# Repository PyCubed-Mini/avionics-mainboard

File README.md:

# avionics-motherboard
Main flight computer board for the PyCubed-Mini spacecraft

[Motherboard block diagram draw.io](https://drive.google.com/file/d/1i8R7Gf3Xthh23wCwzEqk22y6YbL8fg8w/view?usp=sharing)

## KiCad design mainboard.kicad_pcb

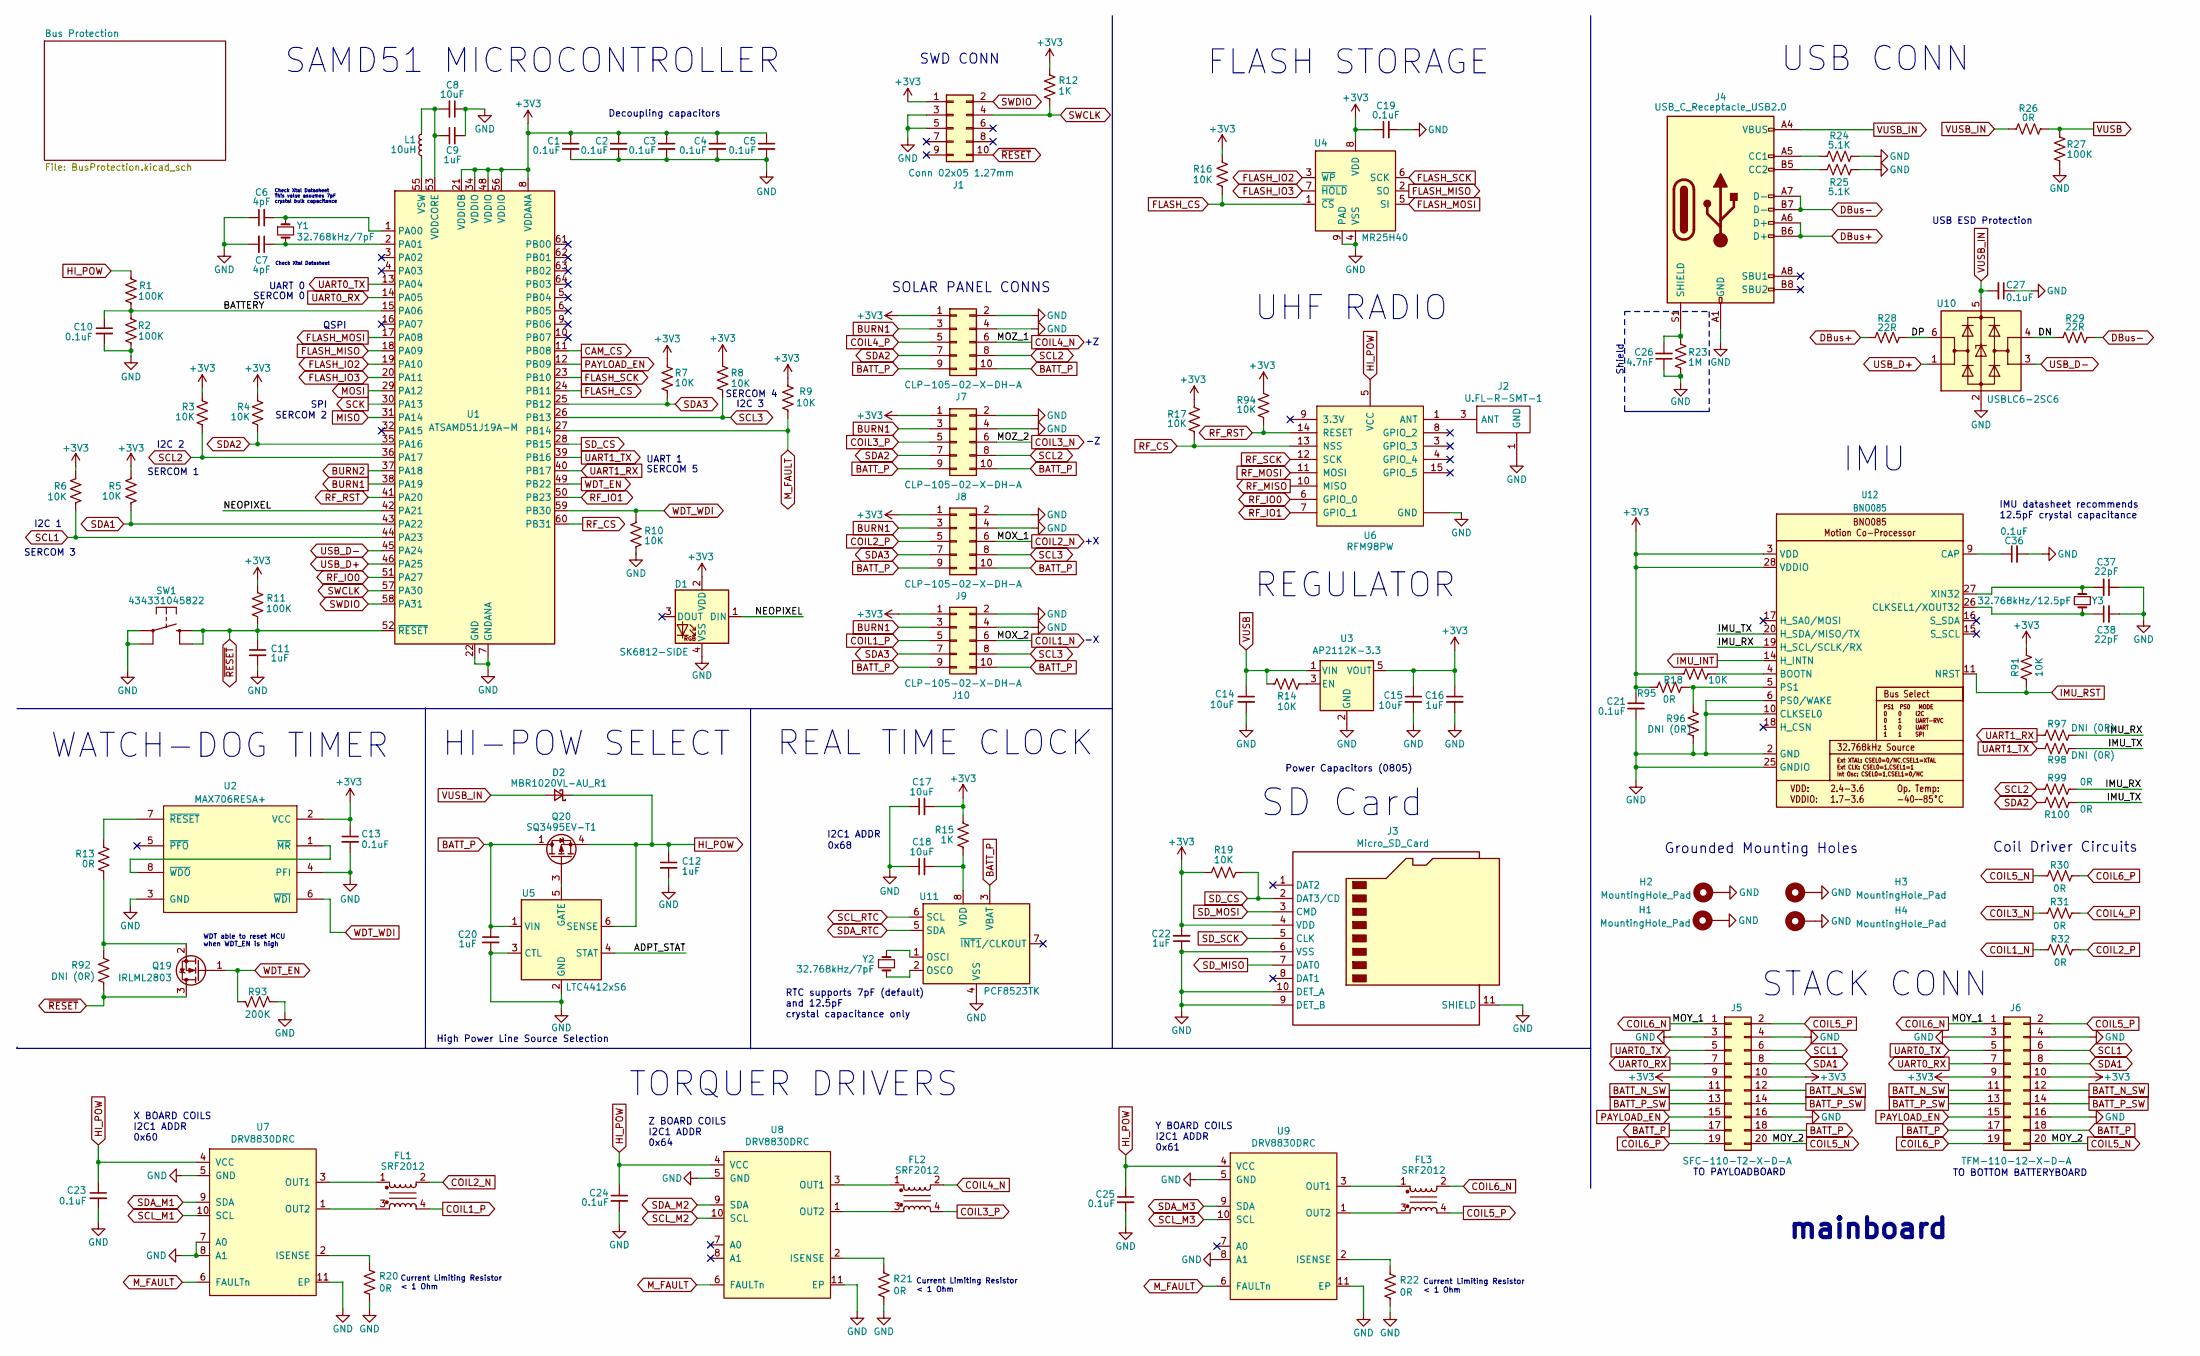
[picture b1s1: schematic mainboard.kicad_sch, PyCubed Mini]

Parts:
C1, C2, C3, C4, C5, C10, C13, C19, C21, C23, C24, C25, C27, C36: 0.1uF; C_0603_1608Metric
C6, C7: 4pF; C_0603_1608Metric
C8, C17, C18: 10uF; C_0603_1608Metric
C9, C11, C12, C20, C22: 1uF; C_0603_1608Metric
C14, C15: 10uF; C_0805_2012Metric
C16: 1uF; C_0805_2012Metric
C26: 4.7nF; C_0603_1608Metric
C37, C38: 22pF; C_0603_1608Metric
D1: SK6812-SIDE
D2: MBR1020VL-AU_R1; D_SOD-123F
FL1, FL2, FL3: SRF2012
H1, H2, H3, H4: MountingHole_Pad; MountingHole
J1: Conn 02x05 1.27mm; PinHeader_2x05_P1.27mm_Vertical_SMD
J2: U.FL-R-SMT-1; Manufacturer_Part_Number U.FL-R-SMT-1
J3: Micro_SD_Card; microSD_104031-0811
J4: USB_C_Receptacle_USB2.0; USB_C_Receptacle_HRO_TYPE-C-31-M-12
J5: SFC-110-T2-X-D-A; SAMTEC_SFC-110-T2-X-D-A
J6: TFM-110-12-X-D-A; SAMTEC_TFM-110-12-X-D-A
J7, J8, J9, J10: CLP-105-02-X-DH-A; SAMTEC_CLP-105-02-X-DH-A
L1: 10uH; L_0805_2012Metric
Q19: IRLML2803; SOT-23
Q20: SQ3495EV-T1; SOT-23-6
R1, R2, R11, R27: 100K; R_0603_1608Metric
R3, R4, R5, R6, R7, R8, R9, R10, R14, R16, R17, R18, R19, R91, R94: 10K; R_0603_1608Metric
R12, R15: 1K; R_0603_1608Metric
R13, R20, R21, R22, R26, R30, R31, R32, R95, R99, R100: 0R; R_0603_1608Metric
R23: 1M; R_0603_1608Metric
R24, R25: 5.1K; R_0603_1608Metric
R28, R29: 22R; R_0603_1608Metric
R92, R96, R97, R98: DNI (0R); R_0603_1608Metric
R93: 200K; R_0603_1608Metric
SW1: 434331045822; SMT_1045822_WRE
U1: ATSAMD51J19A-M; QFN-64-1EP_9x9mm_P0.5mm_EP4.7x4.7mm
U2: MAX706RESA+; SOIC-8_3.9x4.9mm_P1.27mm
U3: AP2112K-3.3; SOT-23-5
U4: MR25H40; MR25H40DF
U5: LTC4412xS6; TSOT-23-6
U6: RFM98PW
U7, U8, U9: DRV8830DRC; VSON-10
U10: USBLC6-2SC6; SOT-23-6
U11: PCF8523TK; HVSON-8-1EP_4x4mm_P0.8mm_EP2.2x3.1mm
U12: BNO085; LGA-28
Y1, Y2: 32.768kHz/7pF; Crystal_SMD_MicroCrystal_CC7V-T1A-2Pin_3.2x1.5mm
Y3: 32.768kHz/12.5pF; Crystal_SMD_MicroCrystal_CC7V-T1A-2Pin_3.2x1.5mm

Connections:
+3V3: C1.1, C2.1, C3.1, C4.1, C5.1, C13.1, C15.1, C16.1, C17.2, C19.1, C21.1, C22.2, D1.2 (VDD), J1.1, J3.4 (VDD), J5.9, J5.10, J6.9, J6.10, J7.1, J8.1, J9.1, J10.1, R3.2, R4.2, R5.2, R6.2, R7.2, R8.2, R9.1, R11.2, R12.2, R15.2, R16.1, R17.2, R18.2, R19.1, R91.2, R94.2, R95.2, U1.8 (VDDANA), U1.21 (VDDIOB), U1.34 (VDDIO), U1.48 (VDDIO), U1.56 (VDDIO), U2.2 (VCC), U3.5 (VOUT), U4.8 (VDD), U12.3 (VDD), U12.28 (VDDIO); also elsewhere on the board
/ADPT_STAT: U5.4 (STAT)
/BATTERY: C10.1, R1.1, R2.2, U1.15 (PA06)
/DN: R29.2, U10.4 (I/O2)
/DP: R28.1, U10.6 (I/O1)
/IMU_RX: R97.2, R99.2, U12.19 (H_SCL/SCLK/RX)
/IMU_TX: R98.2, R100.2, U12.20 (H_SDA/MISO/TX)
/NEOPIXEL: D1.1 (DIN), U1.42 (PA21)
BATT_N_SW: J5.11, J5.12, J6.11, J6.12
BATT_P: C20.1, J5.17, J5.18, J6.17, J6.18, J7.9, J7.10, J8.9, J8.10, J9.9, J9.10, J10.9, J10.10, Q20.1 (D), Q20.2 (D), Q20.5 (D), Q20.6 (D), U5.1 (VIN), U11.3 (VBAT)
BATT_P_SW: J5.13, J5.14, J6.13, J6.14
BURN1: J7.3, J8.3, J9.3, J10.3, U1.38 (PA19)
BURN2: U1.37 (PA18)
CAM_CS: U1.11 (PB08)
COIL1_N: J10.6, R32.1
COIL1_P: FL1.4, J10.5
COIL2_N: FL1.2, J9.6
COIL2_P: J9.5, R32.2
COIL3_N: J8.6, R31.1
COIL3_P: FL2.4, J8.5
COIL4_N: FL2.2, J7.6
COIL4_P: J7.5, R31.2
COIL5_N: J5.20, J6.20, R30.2
COIL5_P: FL3.4, J5.2, J6.2
COIL6_N: FL3.2, J5.1, J6.1
COIL6_P: J5.19, J6.19, R30.1
DBus+: J4.A6 (D+), J4.B6 (D+), R28.2
DBus-: J4.A7 (D-), J4.B7 (D-), R29.1
FLASH_CS: R16.2, U1.24 (PB11), U4.1 (~CS)
FLASH_IO2: U1.19 (PA10), U4.3 (~WP)
FLASH_IO3: U1.20 (PA11), U4.7 (~HOLD)
FLASH_MISO: U1.18 (PA09), U4.2 (SO)
FLASH_MOSI: U1.17 (PA08), U4.5 (SI)
FLASH_SCK: U1.23 (PB10), U4.6 (SCK)
GND: C1.2, C2.2, C3.2, C4.2, C5.2, C6.1, C7.2, C8.1, C9.2, C10.2, C11.2, C12.2, C13.2, C14.2, C15.2, C16.2, C17.1, C18.1, C19.2, C20.2, C21.2, C22.1, C23.2, C24.2, C25.2, C26.1, C27.1, C36.2, C37.1, C38.2, D1.4 (VSS), H1.1, H2.1, H3.1, H4.1, J1.3, J1.5, J2.1 (GND), J2.2, J3.6 (VSS), J3.9 (DET_B), J3.10 (DET_A), J3.11 (SHIELD), J4.A1 (GND), J4.A12 (GND), J4.B1 (GND), J4.B12 (GND), J5.3, J5.4, J5.16, J6.3, J6.4, J6.16, J7.2, J7.4, J8.2, J8.4, J9.2, J9.4, J10.2, J10.4, R2.1, R10.1, R20.1, R21.1, R22.1, R23.1, R24.2, R25.2, R27.2, R93.2, R96.2, SW1.1, SW1.3 (P1), U1.7 (GNDANA), U1.22 (GND), U1.33 (GND), U1.47 (GND), U1.54 (GND), U1.65 (GND), U2.3 (GND), U2.4 (PFI), U3.2 (GND), U4.4 (VSS), U4.9 (PAD), U5.2 (GND), U5.3 (CTL), U6.2 (GND), U6.16 (GND), U6.17 (GND), U7.5 (GND), U7.7 (A0), U7.8 (A1), U7.11 (EP), U8.5 (GND), U8.11 (EP), U9.5 (GND), U9.8 (A1), U9.11 (EP), U10.2 (GND), U11.4 (VSS), U11.9 (VSS), U12.2 (GND), U12.6 (PS0/WAKE), U12.10 (CLKSEL0), U12.25 (GNDIO); also elsewhere on the board
HI_POW: C12.1, C23.1, C24.1, C25.1, D2.1 (K), Q20.4 (S), R1.2, U5.6 (SENSE), U6.5 (VCC), U7.4 (VCC), U8.4 (VCC), U9.4 (VCC)
IMU_INT: U12.14 (H_INTN)
IMU_RST: R91.1, U12.11 (NRST)
MISO: U1.31 (PA14); also elsewhere on the board
MOSI: U1.29 (PA12); also elsewhere on the board
M_FAULT: R9.2, U1.27 (PB14), U7.6 (FAULTn), U8.6 (FAULTn), U9.6 (FAULTn)
unnamed: J2.3 (ANT), U6.1 (ANT)
unnamed: J4.A5 (CC1), R24.1
unnamed: J4.B5 (CC2), R25.1
unnamed: C26.2, J4.S1 (SHIELD), R23.2
unnamed: Q19.2 (S), R13.1, R92.2
unnamed: Q20.3 (G), U5.5 (GATE)
unnamed: C6.2, U1.1 (PA00), Y1.1
unnamed: C7.1, U1.2 (PA01), Y1.2
unnamed: C8.2, C9.1, L1.1, U1.53 (VDDCORE)
unnamed: L1.2, U1.55 (VSW)
unnamed: U2.1 (~MR), U2.8 (~WDO)
unnamed: R13.2, U2.7 (~RESET)
unnamed: R14.2, U3.3 (EN)
unnamed: R20.2, U7.2 (ISENSE)
unnamed: FL1.1, U7.3 (OUT1)
unnamed: FL1.3, U7.1 (OUT2)
unnamed: R21.2, U8.2 (ISENSE)
unnamed: FL2.1, U8.3 (OUT1)
unnamed: FL2.3, U8.1 (OUT2)
unnamed: R22.2, U9.2 (ISENSE)
unnamed: FL3.1, U9.3 (OUT1)
unnamed: FL3.3, U9.1 (OUT2)
unnamed: U11.1 (OSCI), Y2.1
unnamed: U11.2 (OSCO), Y2.2
unnamed: C18.2, R15.1, U11.8 (VDD)
unnamed: R18.1, U12.4 (BOOTN)
unnamed: C36.1, U12.9 (CAP)
unnamed: C38.1, U12.26 (CLKSEL1/XOUT32), Y3.2
unnamed: R95.1, R96.1, U12.5 (PS1)
unnamed: C37.2, U12.27 (XIN32), Y3.1
PAYLOAD_EN: J5.15, J6.15, U1.12 (PB09)
RF_CS: R17.1, U1.60 (PB31), U6.13 (NSS); also elsewhere on the board
RF_IO0: U1.51 (PA27), U6.6 (GPIO_0)
RF_IO1: U1.50 (PB23), U6.7 (GPIO_1)
RF_MISO: U6.10 (MISO); also elsewhere on the board
RF_MOSI: U6.11 (MOSI); also elsewhere on the board
RF_RST: R94.1, U1.41 (PA20), U6.14 (RESET)
RF_SCK: U6.12 (SCK); also elsewhere on the board
SCK: U1.30 (PA13); also elsewhere on the board
SCL1: J5.6, J6.6, R6.1, U1.44 (PA23); also elsewhere on the board
SCL2: J7.8, J8.8, R3.1, R99.1, U1.36 (PA17)
SCL3: J9.8, J10.8, R8.1, U1.26 (PB13)
SCL_M1: U7.10 (SCL); also elsewhere on the board
SCL_M2: U8.10 (SCL); also elsewhere on the board
SCL_M3: U9.10 (SCL); also elsewhere on the board
SCL_RTC: U11.6 (SCL); also elsewhere on the board
SDA1: J5.8, J6.8, R5.1, U1.43 (PA22); also elsewhere on the board
SDA2: J7.7, J8.7, R4.1, R100.1, U1.35 (PA16)
SDA3: J9.7, J10.7, R7.1, U1.25 (PB12)
SDA_M1: U7.9 (SDA); also elsewhere on the board
SDA_M2: U8.9 (SDA); also elsewhere on the board
SDA_M3: U9.9 (SDA); also elsewhere on the board
SDA_RTC: U11.5 (SDA); also elsewhere on the board
SD_CS: J3.2 (DAT3/CD), R19.2, U1.28 (PB15); also elsewhere on the board
SD_MISO: J3.7 (DAT0); also elsewhere on the board
SD_MOSI: J3.3 (CMD); also elsewhere on the board
SD_SCK: J3.5 (CLK); also elsewhere on the board
SWCLK: J1.4, R12.1, U1.57 (PA30)
SWDIO: J1.2, U1.58 (PA31)
UART0_RX: J5.7, J6.7, U1.14 (PA05)
UART0_TX: J5.5, J6.5, U1.13 (PA04)
UART1_RX: R97.1, U1.40 (PB17)
UART1_TX: R98.1, U1.39 (PB16)
USB_D+: U1.46 (PA25), U10.1 (I/O1)
USB_D-: U1.45 (PA24), U10.3 (I/O2)
VUSB: C14.1, R14.1, R26.2, R27.1, U3.1 (VIN)
VUSB_IN: C27.2, D2.2 (A), J4.A4 (VBUS), J4.A9 (VBUS), J4.B4 (VBUS), J4.B9 (VBUS), R26.1, U10.5 (VBUS)
WDT_EN: Q19.1 (G), R93.1, U1.49 (PB22)
WDT_WDI: R10.2, U1.59 (PB30), U2.6 (~WDI)
~RESET: C11.1, J1.10, Q19.3 (D), R11.1, R92.1, SW1.2 (S), SW1.4 (S1), U1.52 (~RESET)

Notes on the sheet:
High Power Line Source Selection
X BOARD COILS I2C1 ADDR 0x60
SERCOM 0
WDT able to reset MCU when WDT_EN is high
Current Limiting Resistor < 1 Ohm
mainboard
0x68
SAMD51 MICROCONTROLLER
FLASH STORAGE
UART 1
USB ESD Protection
REGULATOR
UART 0
SOLAR PANEL CONNS
SPI
I2C 3
Check Xtal Datasheet
IMU datasheet recommends 12.5pF crystal capacitance
TO BOTTOM BATTERYBOARD
TORQUER DRIVERS
WATCH-DOG TIMER
SWD CONN
SERCOM 1
Coil Driver Circuits
STACK CONN
Shield
SERCOM 5
Decoupling capacitors
I2C 2
SERCOM 3
Z BOARD COILS I2C1 ADDR 0x64
IMU
UHF RADIO
SERCOM 2
Check Xtal Datasheet This value assumes 7pF crystal bulk capacitance
I2C 1
SERCOM 4
Grounded Mounting Holes
USB CONN
SD Card

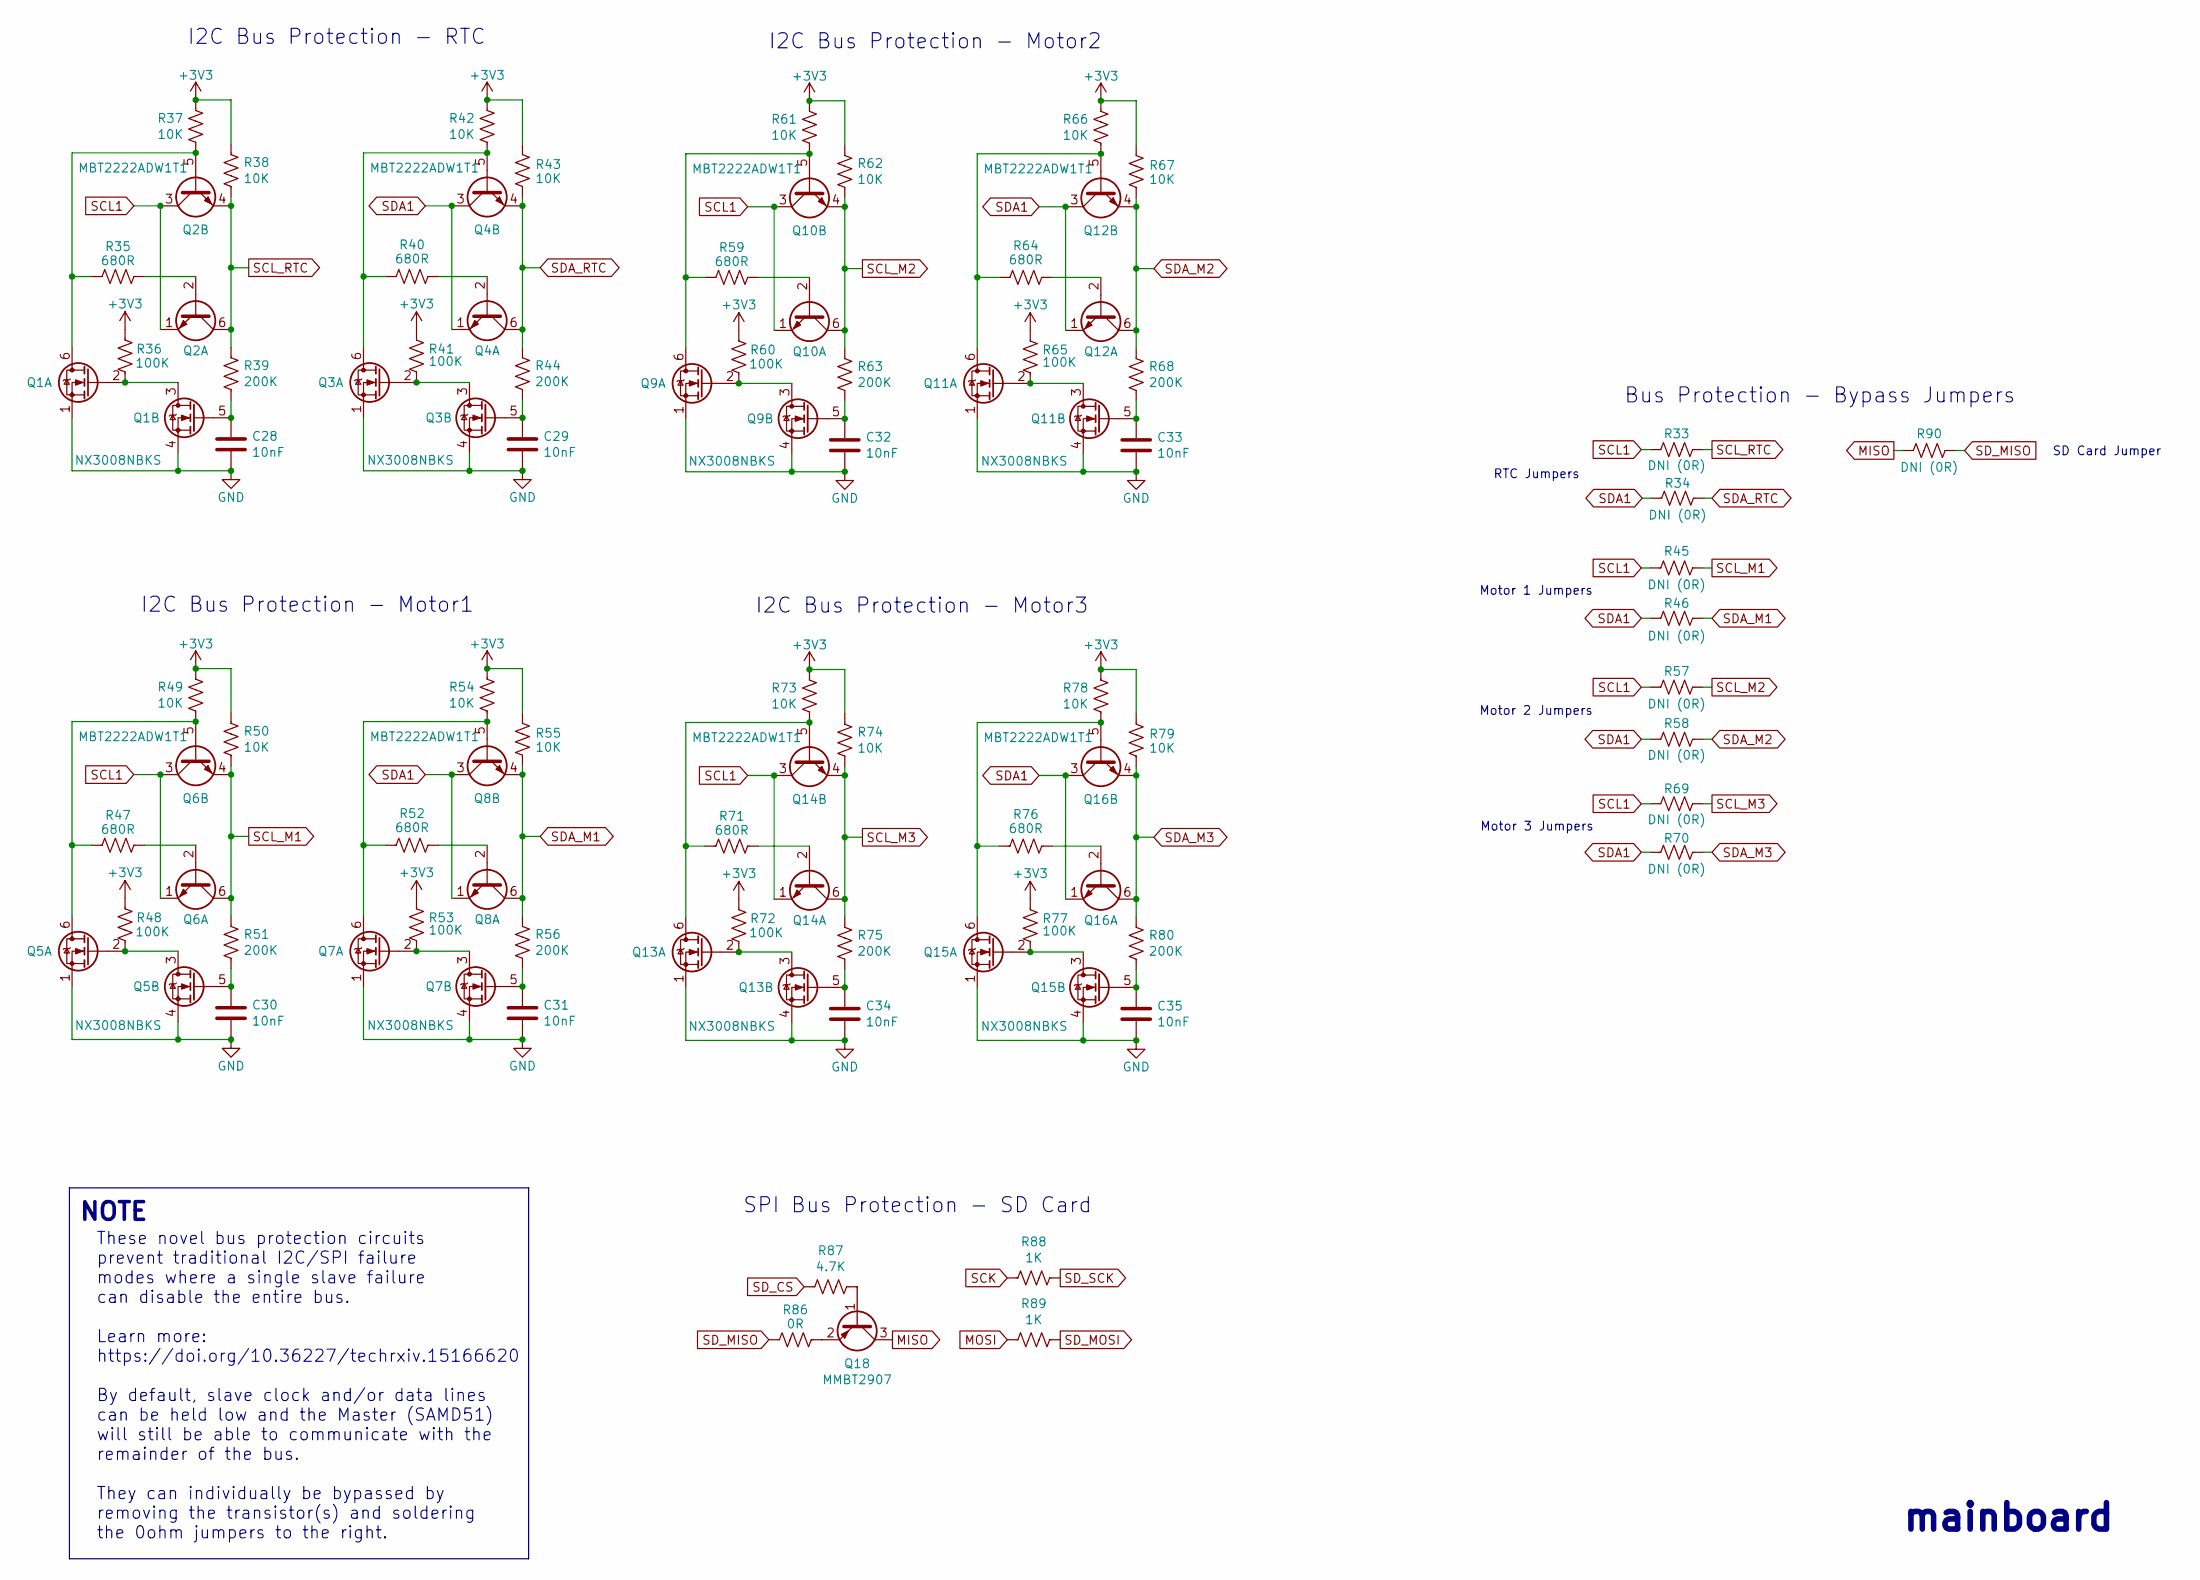
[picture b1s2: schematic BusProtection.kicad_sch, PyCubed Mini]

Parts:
C28, C29, C30, C31, C32, C33, C34, C35: 10nF; C_0603_1608Metric
Q1, Q3, Q5, Q7, Q9, Q11, Q13, Q15: NX3008NBKS; SOT-363_SC-70-6; Manufacturer_Part_Number NX3008NBKS
Q2, Q4, Q6, Q8, Q10, Q12, Q14, Q16: MBT2222ADW1T1; SOT-363_SC-70-6; Manufacturer_Part_Number MBT2222ADW1T1G
Q18: MMBT2907; SOT-23; Manufacturer_Part_Number MMBT2907ALT1G
R33, R34, R45, R46, R57, R58, R69, R70, R90: DNI (0R); R_0603_1608Metric
R35, R40, R47, R52, R59, R64, R71, R76: 680R; R_0603_1608Metric
R36, R41, R48, R53, R60, R65, R72, R77: 100K; R_0603_1608Metric
R37, R38, R42, R43, R49, R50, R54, R55, R61, R62, R66, R67, R73, R74, R78, R79: 10K; R_0603_1608Metric
R39, R44, R51, R56, R63, R68, R75, R80: 200K; R_0603_1608Metric
R86: 0R; R_0603_1608Metric
R87: 4.7K; R_0603_1608Metric
R88, R89: 1K; R_0603_1608Metric

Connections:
+3V3: R36.1, R37.1, R38.1, R41.1, R42.1, R43.1, R48.1, R49.1, R50.1, R53.1, R54.1, R55.1, R60.1, R61.1, R62.1, R65.1, R66.1, R67.1, R72.1, R73.1, R74.1, R77.1, R78.1, R79.1; also elsewhere on the board
GND: C28.2, C29.2, C30.2, C31.2, C32.2, C33.2, C34.2, C35.2, Q1.1 (S2), Q1.4 (S1), Q3.1 (S2), Q3.4 (S1), Q5.1 (S2), Q5.4 (S1), Q7.1 (S2), Q7.4 (S1), Q9.1 (S2), Q9.4 (S1), Q11.1 (S2), Q11.4 (S1), Q13.1 (S2), Q13.4 (S1), Q15.1 (S2), Q15.4 (S1); also elsewhere on the board
MISO: Q18.3 (C), R90.2; also elsewhere on the board
MOSI: R89.2; also elsewhere on the board
unnamed: Q1.6 (D1), Q2.5 (B2), R35.2, R37.2
unnamed: Q1.2 (G2), Q1.3 (D2), R36.2
unnamed: C28.1, Q1.5 (G1), R39.2
unnamed: Q2.2 (B1), R35.1
unnamed: Q3.6 (D1), Q4.5 (B2), R40.2, R42.2
unnamed: Q3.2 (G2), Q3.3 (D2), R41.2
unnamed: C29.1, Q3.5 (G1), R44.2
unnamed: Q4.2 (B1), R40.1
unnamed: Q5.6 (D1), Q6.5 (B2), R47.2, R49.2
unnamed: Q5.2 (G2), Q5.3 (D2), R48.2
unnamed: C30.1, Q5.5 (G1), R51.2
unnamed: Q6.2 (B1), R47.1
unnamed: Q7.6 (D1), Q8.5 (B2), R52.2, R54.2
unnamed: Q7.2 (G2), Q7.3 (D2), R53.2
unnamed: C31.1, Q7.5 (G1), R56.2
unnamed: Q8.2 (B1), R52.1
unnamed: Q9.2 (G2), Q9.3 (D2), R60.2
unnamed: C32.1, Q9.5 (G1), R63.2
unnamed: Q10.2 (B1), R59.1
unnamed: Q9.6 (D1), Q10.5 (B2), R59.2, R61.2
unnamed: Q11.6 (D1), Q12.5 (B2), R64.2, R66.2
unnamed: Q11.2 (G2), Q11.3 (D2), R65.2
unnamed: C33.1, Q11.5 (G1), R68.2
unnamed: Q12.2 (B1), R64.1
unnamed: Q13.6 (D1), Q14.5 (B2), R71.2, R73.2
unnamed: Q13.2 (G2), Q13.3 (D2), R72.2
unnamed: C34.1, Q13.5 (G1), R75.2
unnamed: Q14.2 (B1), R71.1
unnamed: Q15.6 (D1), Q16.5 (B2), R76.2, R78.2
unnamed: Q15.2 (G2), Q15.3 (D2), R77.2
unnamed: C35.1, Q15.5 (G1), R80.2
unnamed: Q16.2 (B1), R76.1
unnamed: Q18.1 (B), R87.1
unnamed: Q18.2 (E), R86.1
SCK: R88.2; also elsewhere on the board
SCL1: Q2.1 (E1), Q2.3 (C2), Q6.1 (E1), Q6.3 (C2), Q10.1 (E1), Q10.3 (C2), Q14.1 (E1), Q14.3 (C2), R33.2, R45.2, R57.2, R69.2; also elsewhere on the board
SCL_M1: Q6.4 (E2), Q6.6 (C1), R45.1, R50.2, R51.1; also elsewhere on the board
SCL_M2: Q10.4 (E2), Q10.6 (C1), R57.1, R62.2, R63.1; also elsewhere on the board
SCL_M3: Q14.4 (E2), Q14.6 (C1), R69.1, R74.2, R75.1; also elsewhere on the board
SCL_RTC: Q2.4 (E2), Q2.6 (C1), R33.1, R38.2, R39.1; also elsewhere on the board
SDA1: Q4.1 (E1), Q4.3 (C2), Q8.1 (E1), Q8.3 (C2), Q12.1 (E1), Q12.3 (C2), Q16.1 (E1), Q16.3 (C2), R34.2, R46.2, R58.2, R70.2; also elsewhere on the board
SDA_M1: Q8.4 (E2), Q8.6 (C1), R46.1, R55.2, R56.1; also elsewhere on the board
SDA_M2: Q12.4 (E2), Q12.6 (C1), R58.1, R67.2, R68.1; also elsewhere on the board
SDA_M3: Q16.4 (E2), Q16.6 (C1), R70.1, R79.2, R80.1; also elsewhere on the board
SDA_RTC: Q4.4 (E2), Q4.6 (C1), R34.1, R43.2, R44.1; also elsewhere on the board
SD_CS: R87.2; also elsewhere on the board
SD_MISO: R86.2, R90.1; also elsewhere on the board
SD_MOSI: R89.1; also elsewhere on the board
SD_SCK: R88.1; also elsewhere on the board

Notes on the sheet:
Motor 3 Jumpers
I2C Bus Protection - RTC
I2C Bus Protection - Motor3
I2C Bus Protection - Motor2
Motor 1 Jumpers
NOTE
SPI Bus Protection - SD Card
Bus Protection - Bypass Jumpers
I2C Bus Protection - Motor1
RTC Jumpers
mainboard
SD Card Jumper
Motor 2 Jumpers
These novel bus protection circuits prevent traditional I2C/SPI failure modes where a single slave failure can disable the entire bus. Learn more: https://doi.org/10.36227/techrxiv.15166620 By default, slave clock and/or data lines can be held low and the Master (SAMD51) will still be able to commu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

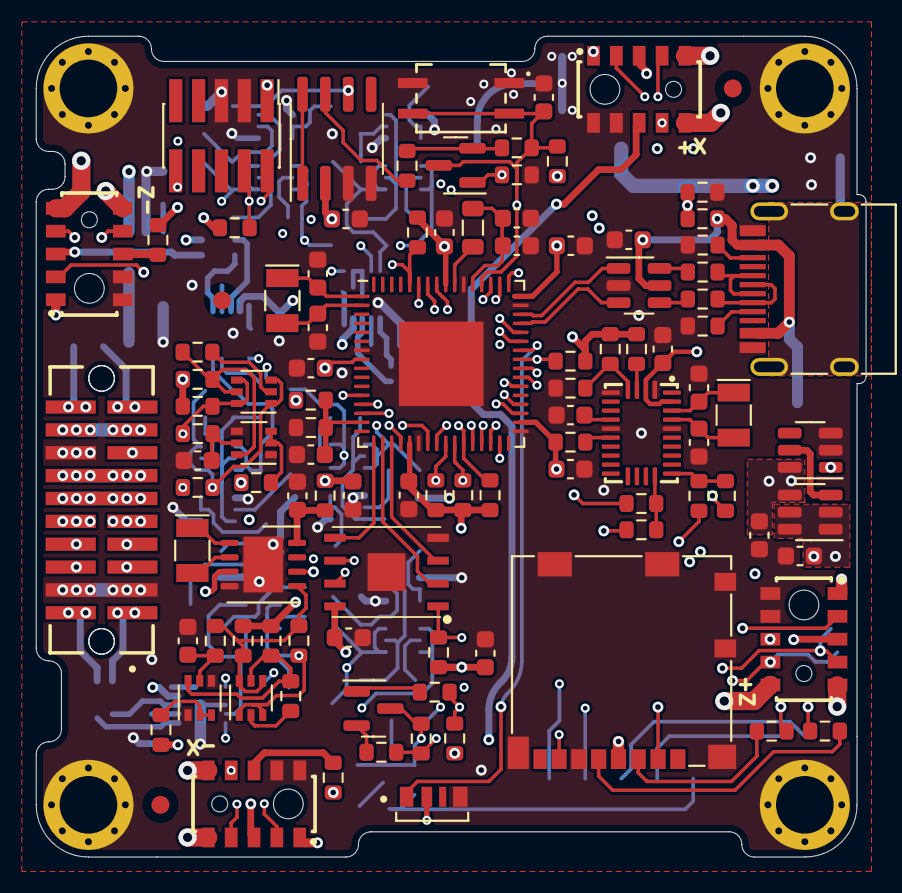
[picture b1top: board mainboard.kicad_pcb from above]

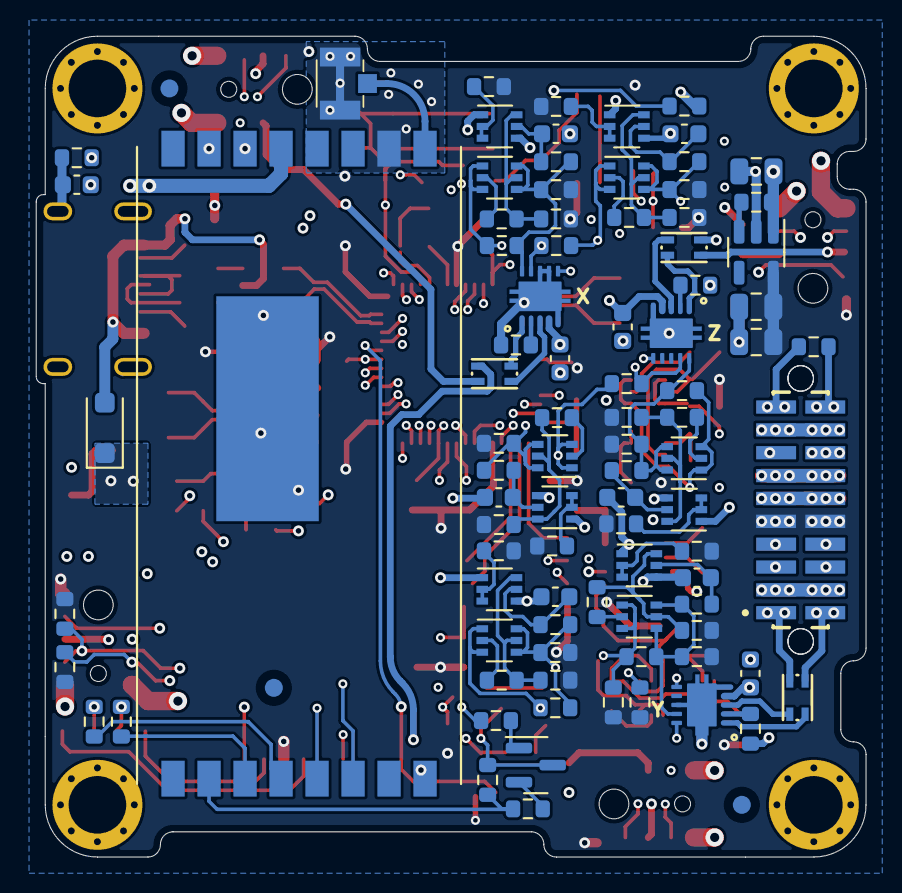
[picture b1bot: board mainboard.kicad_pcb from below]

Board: 4 copper layers, 46.1 x 45.6 mm, 195 parts (89 on the bottom side), 143 nets.

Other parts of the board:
Q17: MMBT2907; SOT-23
R81: 0R; R_0603_1608Metric
R82: 4.7K; R_0603_1608Metric
R83, R84: 1K; R_0603_1608Metric
R85: DNI (0R); R_0603_1608Metric
Ref**: Val**; pycubed_mini_half

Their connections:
MISO: Q17.3 (C), R85.2; also elsewhere on the board
MOSI: R84.2; also elsewhere on the board
unnamed: Q17.1 (B), R82.1
unnamed: Q17.2 (E), R81.1
RF_CS: R82.2; also elsewhere on the board
RF_MISO: R81.2, R85.1; also elsewhere on the board
RF_MOSI: R84.1; also elsewhere on the board
RF_SCK: R83.1; also elsewhere on the board
SCK: R83.2; also elsewhere on the board

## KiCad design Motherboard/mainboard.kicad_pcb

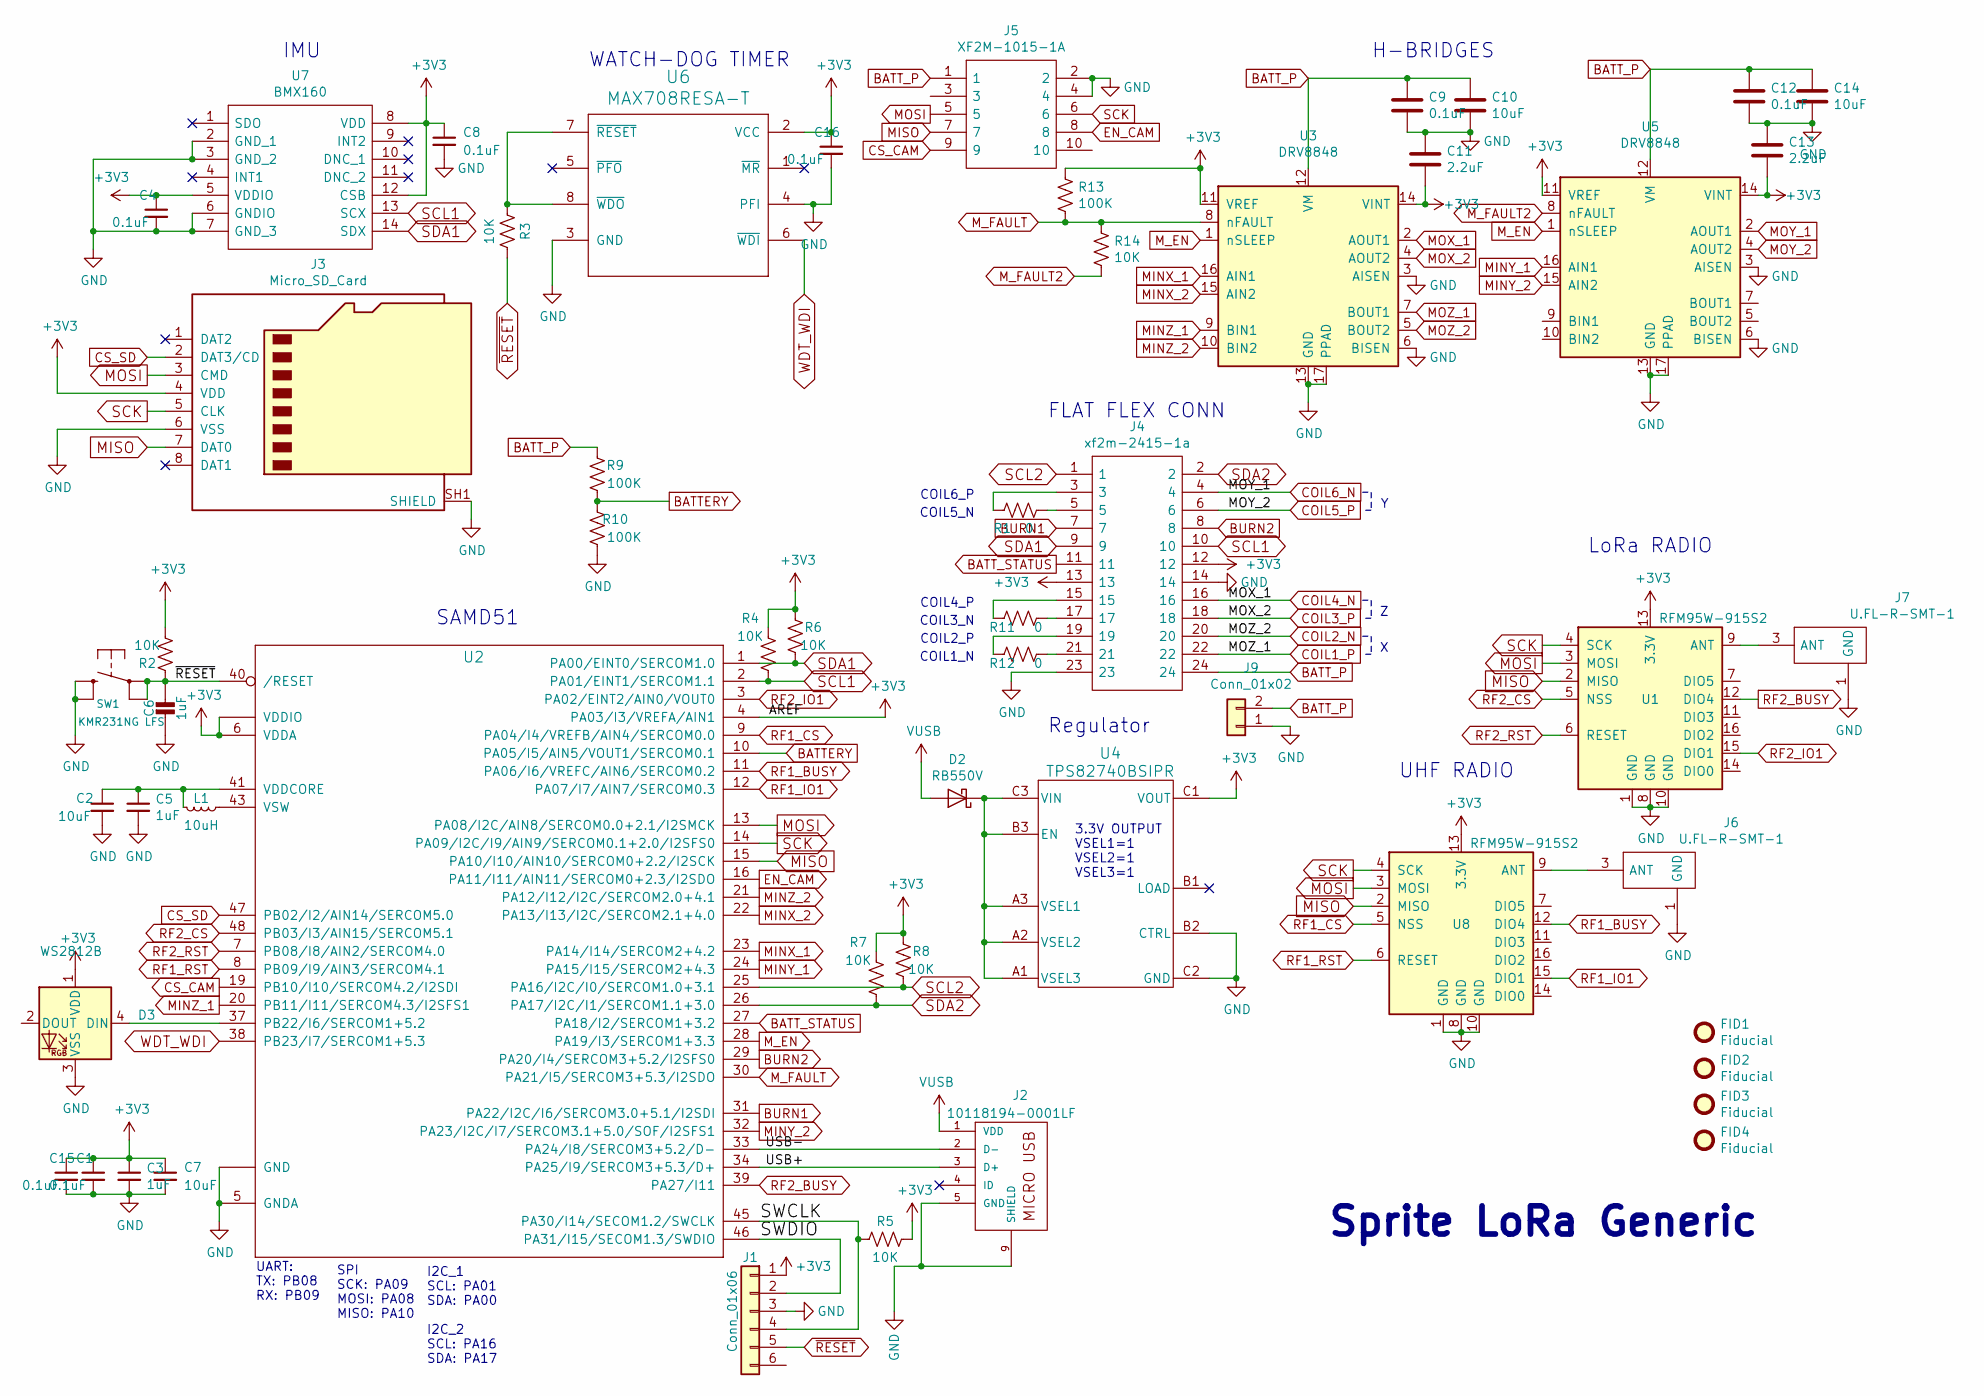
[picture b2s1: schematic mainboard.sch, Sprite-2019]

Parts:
C1, C4, C8, C9, C12, C15, C16: 0.1uF; C_0402_1005Metric
C2, C7, C10, C14: 10uF; C_0402_1005Metric
C3, C5, C6: 1uF; C_0402_1005Metric
C11, C13: 2.2uF; C_0402_1005Metric
D2: RB550V; D_SOD-323
D3: WS2812B; LED_WS2812B_PLCC4_5.0x5.0mm_P3.2mm
FID1, FID2, FID3, FID4: Fiducial; Fiducial_1mm_Silkscreen
J1: Conn_01x06; PinHeader_2x03_P1.27mm_Vertical_SMD
J2: 10118194-0001LF
J3: Micro_SD_Card; 503182-1853_MOLEX-MicroSD
J4: xf2m-2415-1a; XF2M-2415-1A
J5: XF2M-1015-1A; Manufacturer_Part_Number XF2M-1015-1A; Mouser Part Number 653-XF2M-1015-1A
J6, J7: U.FL-R-SMT-1; Manufacturer_Part_Number U.FL-R-SMT-1
J9: Conn_01x02; PinHeader_1x02_P2.54mm_Vertical
L1: 10uH; L_0805_2012Metric
R1, R11, R12: 0; R_0402_1005Metric
R2, R3, R4, R5, R6, R7, R8, R14: 10K; R_0402_1005Metric
R9, R10, R13: 100K; R_0402_1005Metric
SW1: KMR231NG LFS; BTN_KMR2_4.6X2.8
U1, U8: RFM95W-915S2; HOPERF_RFM9XW_SMD
U2: ATSAMD51G_TQFN48; QFN50P700X700X90-49N-D
U3, U5: DRV8848; SOP65P640X120-17N
U4: TPS82740BSIPR; TPS82740ASIPR
U6: MAX708RESA-T; SO-8_3.9x4.9mm_P1.27mm
U7: BMX160; Manufacturer_Part_Number BMX160; Mouser Part Number 262-BMX160

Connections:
+3V3: C1.1, C3.1, C4.1, C7.1, C8.1, C11.2, C13.2, C15.1, C16.1, D3.1 (VDD), J1.1, J3.4 (VDD), J4.12, J4.13, R2.2, R4.2, R5.1, R6.2, R7.2, R8.2, R13.2, U1.13 (3.3V), U2.4 (PA03/I3/VREFA/AIN1), U2.6 (VDDA), U2.17 (VDDIO), U2.36 (VDDIO), U2.44 (VDDIO), U3.11 (VREF), U3.14 (VINT), U4.C1 (VOUT), U5.11 (VREF), U5.14 (VINT), U6.2 (VCC), U7.5 (VDDIO), U7.8 (VDD), U7.12 (CSB), U8.13 (3.3V)
/SWCLK: J1.4, R5.2, U2.45 (PA30/I14/SECOM1.2/SWCLK)
/SWDIO: J1.2, U2.46 (PA31/I15/SECOM1.3/SWDIO)
/USB+: J2.3 (D+), U2.34 (PA25/I9/SERCOM3+5.3/D+)
/USB-: J2.2 (D-), U2.33 (PA24/I8/SERCOM3+5.2/D-)
BATTERY: R9.1, R10.2, U2.10 (PA05/I5/AIN5/VOUT1/SERCOM0.1)
BATT_P: C9.1, C10.1, C12.1, C14.1, J4.24, J5.1, J9.2, R9.2, U3.12 (VM), U5.12 (VM)
BATT_STATUS: J4.11, U2.27 (PA18/I2/SERCOM1+3.2)
BURN1: J4.7, U2.31 (PA22/I2C/I6/SERCOM3.0+5.1/I2SDI)
BURN2: J4.8, U2.29 (PA20/I4/SERCOM3+5.2/I2SFS0)
COIL1_P: J4.22, U3.7 (BOUT1)
COIL2_N: J4.20, U3.5 (BOUT2)
COIL3_P: J4.18, U3.4 (AOUT2)
COIL4_N: J4.16, U3.2 (AOUT1)
COIL5_P: J4.6, U5.4 (AOUT2)
COIL6_N: J4.4, U5.2 (AOUT1)
CS_CAM: J5.9, U2.19 (PB10/I10/SERCOM4.2/I2SDI)
CS_SD: J3.2 (DAT3/CD), U2.47 (PB02/I2/AIN14/SERCOM5.0)
EN_CAM: J5.8, U2.16 (PA11/I11/AIN11/SERCOM0+2.3/I2SDO)
GND: C1.2, C2.2, C3.2, C4.2, C5.2, C6.1, C7.2, C8.2, C9.2, C10.2, C11.1, C12.2, C13.1, C14.2, C15.2, C16.2, D3.3 (VSS), J1.3, J2.5 (GND), J2.8, J2.9 (SHIELD), J3.6 (VSS), J3.SH1 (SHIELD), J4.14, J4.23, J5.2, J5.4, J6.1 (GND), J6.2, J7.1 (GND), J7.2, J9.1, R10.1, SW1.B (S), SW1.B' (S1), U1.1 (GND), U1.8 (GND), U1.10 (GND), U2.5 (GNDA), U2.18 (GND), U2.35 (GND), U2.42 (GND), U2.49, U3.3 (AISEN), U3.6 (BISEN), U3.13 (GND), U3.17 (PPAD), U4.B2 (CTRL), U4.C2 (GND), U5.3 (AISEN), U5.6 (BISEN), U5.13 (GND), U5.17 (PPAD), U6.3 (GND), U6.4 (PFI), U7.2 (GND_1), U7.3 (GND_2), U7.6 (GNDIO), U7.7 (GND_3), U8.1 (GND), U8.8 (GND), U8.10 (GND)
MINX_1: U2.23 (PA14/I14/SERCOM2+4.2), U3.16 (AIN1)
MINX_2: U2.22 (PA13/I13/I2C/SERCOM2.1+4.0), U3.15 (AIN2)
MINY_1: U2.24 (PA15/I15/SERCOM2+4.3), U5.16 (AIN1)
MINY_2: U2.32 (PA23/I2C/I7/SERCOM3.1+5.0/SOF/I2SFS1), U5.15 (AIN2)
MINZ_1: U2.20 (PB11/I11/SERCOM4.3/I2SFS1), U3.9 (BIN1)
MINZ_2: U2.21 (PA12/I12/I2C/SERCOM2.0+4.1), U3.10 (BIN2)
MISO: J3.7 (DAT0), J5.7, U1.2 (MISO), U2.15 (PA10/I10/AIN10/SERCOM0+2.2/I2SCK), U8.2 (MISO)
MOSI: J3.3 (CMD), J5.5, U1.3 (MOSI), U2.13 (PA08/I2C/AIN8/SERCOM0.0+2.1/I2SMCK), U8.3 (MOSI)
M_EN: U2.28 (PA19/I3/SERCOM1+3.3), U3.1 (nSLEEP), U5.1 (nSLEEP)
M_FAULT: R13.1, R14.1, U2.30 (PA21/I5/SERCOM3+5.3/I2SDO), U3.8 (nFAULT)
M_FAULT2: R14.2, U5.8 (nFAULT)
unnamed: C2.1, C5.1, L1.2, U2.41 (VDDCORE)
unnamed: D2.1 (K), U4.A1 (VSEL3), U4.A2 (VSEL2), U4.A3 (VSEL1), U4.B3 (EN), U4.C3 (VIN)
unnamed: D3.4 (DIN), U2.37 (PB22/I6/SERCOM1+5.2)
unnamed: J4.3, R1.1
unnamed: J4.5, R1.2
unnamed: J4.15, R11.1
unnamed: J4.17, R11.2
unnamed: J4.19, R12.1
unnamed: J4.21, R12.2
unnamed: J6.3 (ANT), U8.9 (ANT)
unnamed: J7.3 (ANT), U1.9 (ANT)
unnamed: L1.1, U2.43 (VSW)
unnamed: R3.2, U6.7 (~RESET), U6.8 (~WDO)
RF1_BUSY: U2.11 (PA06/I6/VREFC/AIN6/SERCOM0.2), U8.12 (DIO4)
RF1_CS: U2.9 (PA04/I4/VREFB/AIN4/SERCOM0.0), U8.5 (NSS)
RF1_IO1: U2.12 (PA07/I7/AIN7/SERCOM0.3), U8.15 (DIO1)
RF1_RST: U2.8 (PB09/I9/AIN3/SERCOM4.1), U8.6 (RESET)
RF2_BUSY: U1.12 (DIO4), U2.39 (PA27/I11)
RF2_CS: U1.5 (NSS), U2.48 (PB03/I3/AIN15/SERCOM5.1)
RF2_IO1: U1.15 (DIO1), U2.3 (PA02/EINT2/AIN0/VOUT0)
RF2_RST: U1.6 (RESET), U2.7 (PB08/I8/AIN2/SERCOM4.0)
SCK: J3.5 (CLK), J5.6, U1.4 (SCK), U2.14 (PA09/I2C/I9/AIN9/SERCOM0.1+2.0/I2SFS0), U8.4 (SCK)
SCL1: J4.10, R4.1, U2.2 (PA01/EINT1/SERCOM1.1), U7.13 (SCX)
SCL2: J4.1, R8.1, U2.25 (PA16/I2C/I0/SERCOM1.0+3.1)
SDA1: J4.9, R6.1, U2.1 (PA00/EINT0/SERCOM1.0), U7.14 (SDX)
SDA2: J4.2, R7.1, U2.26 (PA17/I2C/I1/SERCOM1.1+3.0)
VUSB: D2.2 (A), J2.1 (VDD)
WDT_WDI: U2.38 (PB23/I7/SERCOM1+5.3), U6.6 (~WDI)
~RESET: C6.2, J1.5, R2.1, R3.1, SW1.A, SW1.A' (P1), U2.40 (/RESET)

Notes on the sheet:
Regulator
3.3V OUTPUT VSEL1=1 VSEL2=1 VSEL3=1
SAMD51
UHF RADIO
Sprite LoRa Generic
LoRa RADIO
H-BRIDGES
WATCH-DOG TIMER
IMU
FLAT FLEX CONN
UART: TX: PB08 RX: PB09
SPI SCK: PA09 MOSI: PA08 MISO: PA10
I2C_1 SCL: PA01 SDA: PA00 I2C_2 SCL: PA16 SDA: PA17
COIL1_N
COIL3_N
COIL2_P
COIL4_P
COIL5_N
COIL6_P

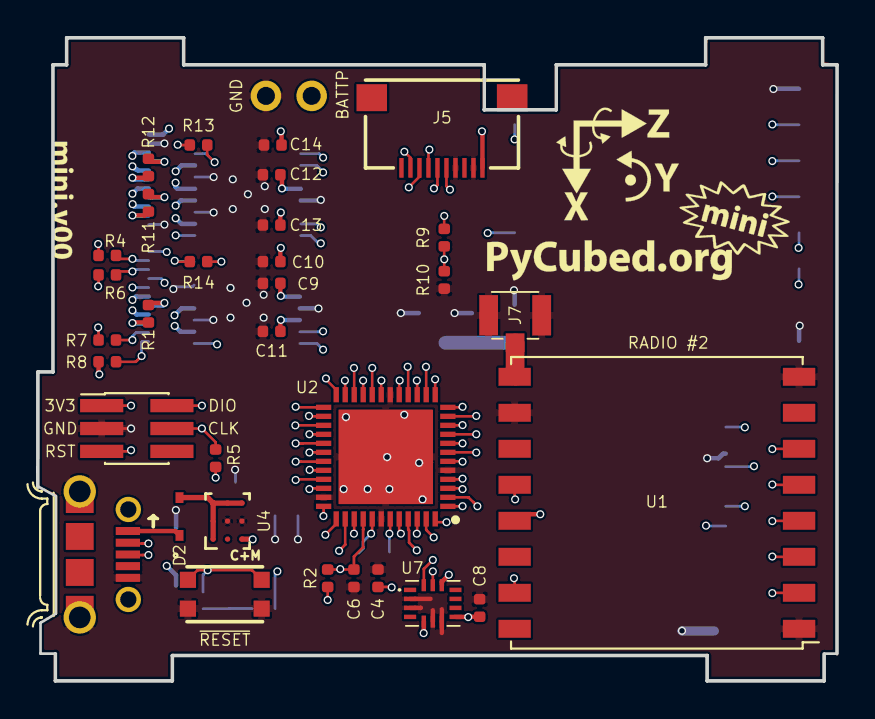
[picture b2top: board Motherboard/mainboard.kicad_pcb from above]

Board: 4 copper layers, 44.4 x 35.7 mm, 60 parts (0 on the bottom side), 60 nets.

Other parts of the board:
Ref**: Val**; XYZ_mini
Ref**#2: Val**; holliday
Ref**#3, Ref**#4: Val**; version
Ref**#5, Ref**#6: Val**; pycubed_mini_logo

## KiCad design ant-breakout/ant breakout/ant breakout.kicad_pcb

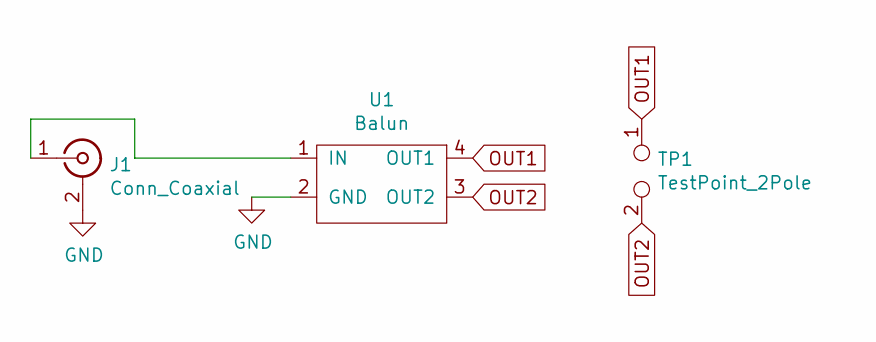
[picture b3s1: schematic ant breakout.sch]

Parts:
J1: Conn_Coaxial; SAMTEC_SMA-J-P-H-RA-TH1
TP1: TestPoint_2Pole; exposed pad
U1: Balun

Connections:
GND: J1.2 (Ext), U1.2 (GND)
unnamed: J1.1 (In), U1.1 (IN)
OUT1: TP1.1, U1.4 (OUT1)
OUT2: TP1.2, U1.3 (OUT2)

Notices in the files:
parts and their libraries:
Copyright 2016 Accelerated Designs. All rights reserved.
